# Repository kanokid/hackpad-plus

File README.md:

# Hackpad+
This is a hackpad that I made for Blueprint.
* It uses the Seeed Studio XIAO RP2040
* It has per-key shine through RGB
* It has 9 MX style switches and a rotary encoder for media controls/volume.
* The keys are through a 
* It uses KMK configured through pog for the firmware

Schematic:

PCB:

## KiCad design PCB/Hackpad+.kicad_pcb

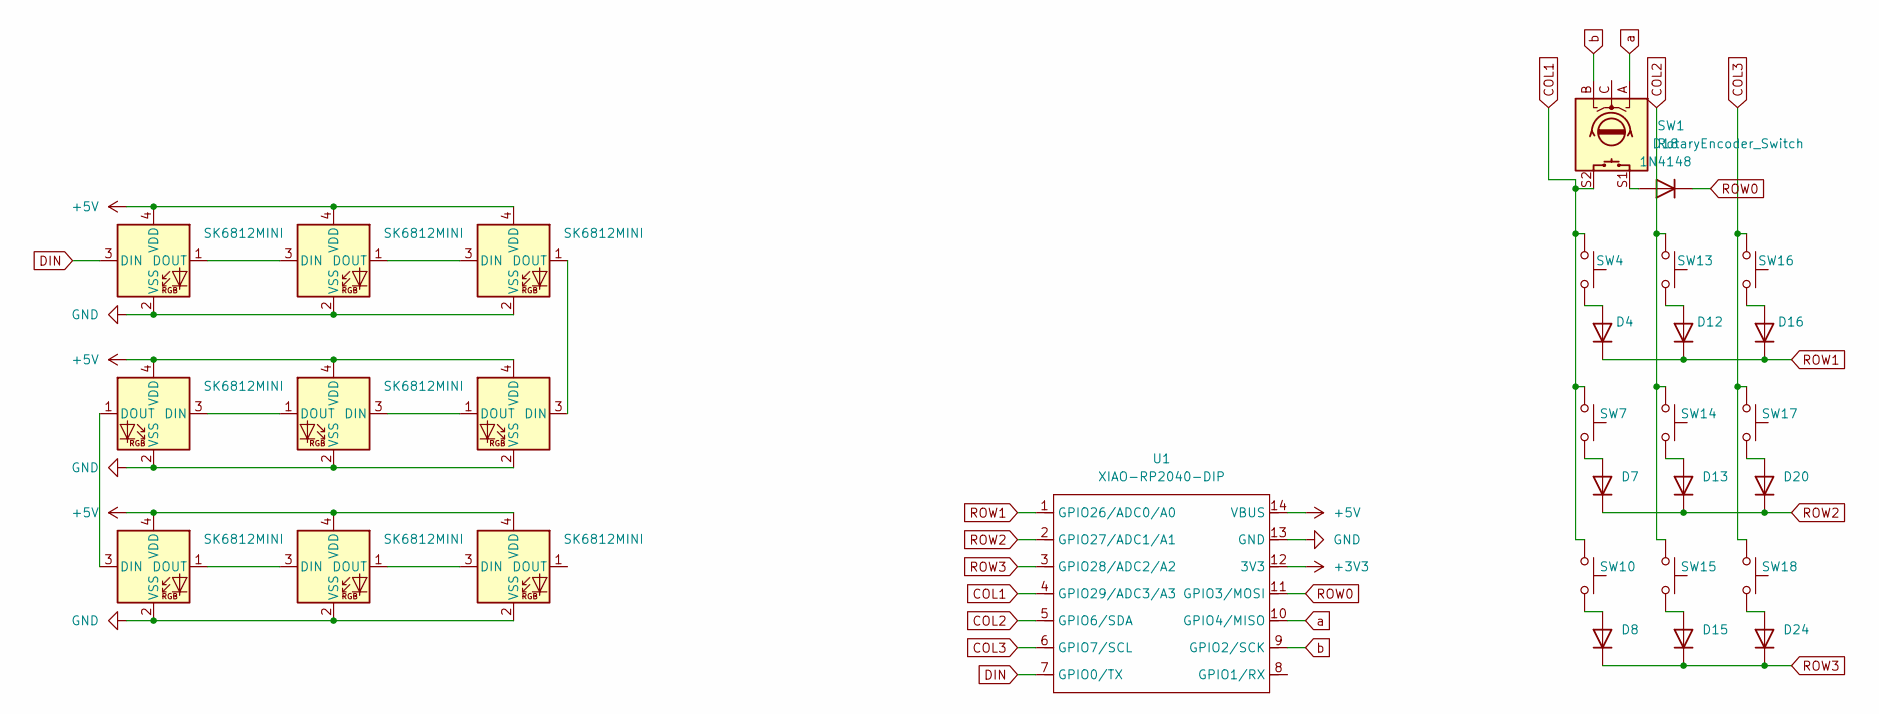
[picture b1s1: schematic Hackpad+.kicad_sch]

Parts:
D1, D2, D3, D5, D6, D9, D10, D11, D14: SK6812MINI; MX_SK6812MINI-E
D4, D7, D8, D12, D13, D15, D16, D18, D20, D24: 1N4148; D_DO-35_SOD27_P7.62mm_Horizontal
SW1: RotaryEncoder_Switch; RotaryEncoder_Alps_EC11E-Switch_Vertical_H20mm
SW4, SW7, SW10, SW13, SW14, SW15, SW16, SW17, SW18: SW_Push; SW_Cherry_MX_1.00u_PCB
U1: XIAO-RP2040-DIP

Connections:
+3V3: U1.12 (3V3)
+5V: D1.4 (VDD), D2.4 (VDD), D3.4 (VDD), D5.4 (VDD), D6.4 (VDD), D9.4 (VDD), D10.4 (VDD), D11.4 (VDD), D14.4 (VDD), U1.14 (VBUS)
COL1: SW1.S2, SW4.1, SW7.1, SW10.1, U1.4 (GPIO29/ADC3/A3)
COL2: SW13.1, SW14.1, SW15.1, U1.5 (GPIO6/SDA)
COL3: SW16.1, SW17.1, SW18.1, U1.6 (GPIO7/SCL)
DIN: D1.3 (DIN), U1.7 (GPIO0/TX)
GND: D1.2 (VSS), D2.2 (VSS), D3.2 (VSS), D5.2 (VSS), D6.2 (VSS), D9.2 (VSS), D10.2 (VSS), D11.2 (VSS), D14.2 (VSS), U1.13 (GND)
unnamed: D1.1 (DOUT), D2.3 (DIN)
unnamed: D2.1 (DOUT), D9.3 (DIN)
unnamed: D3.3 (DIN), D9.1 (DOUT)
unnamed: D4.2 (A), SW4.2
unnamed: D5.1 (DOUT), D6.3 (DIN)
unnamed: D7.2 (A), SW7.2
unnamed: D8.2 (A), SW10.2
unnamed: D3.1 (DOUT), D10.3 (DIN)
unnamed: D10.1 (DOUT), D14.3 (DIN)
unnamed: D6.1 (DOUT), D11.3 (DIN)
unnamed: D12.2 (A), SW13.2
unnamed: D13.2 (A), SW14.2
unnamed: D5.3 (DIN), D14.1 (DOUT)
unnamed: D15.2 (A), SW15.2
unnamed: D16.2 (A), SW16.2
unnamed: D18.2 (A), SW1.S1
unnamed: D20.2 (A), SW17.2
unnamed: D24.2 (A), SW18.2
ROW0: D18.1 (K), U1.11 (GPIO3/MOSI)
ROW1: D4.1 (K), D12.1 (K), D16.1 (K), U1.1 (GPIO26/ADC0/A0)
ROW2: D7.1 (K), D13.1 (K), D20.1 (K), U1.2 (GPIO27/ADC1/A1)
ROW3: D8.1 (K), D15.1 (K), D24.1 (K), U1.3 (GPIO28/ADC2/A2)
a: SW1.A, U1.10 (GPIO4/MISO)
b: SW1.B, U1.9 (GPIO2/SCK)

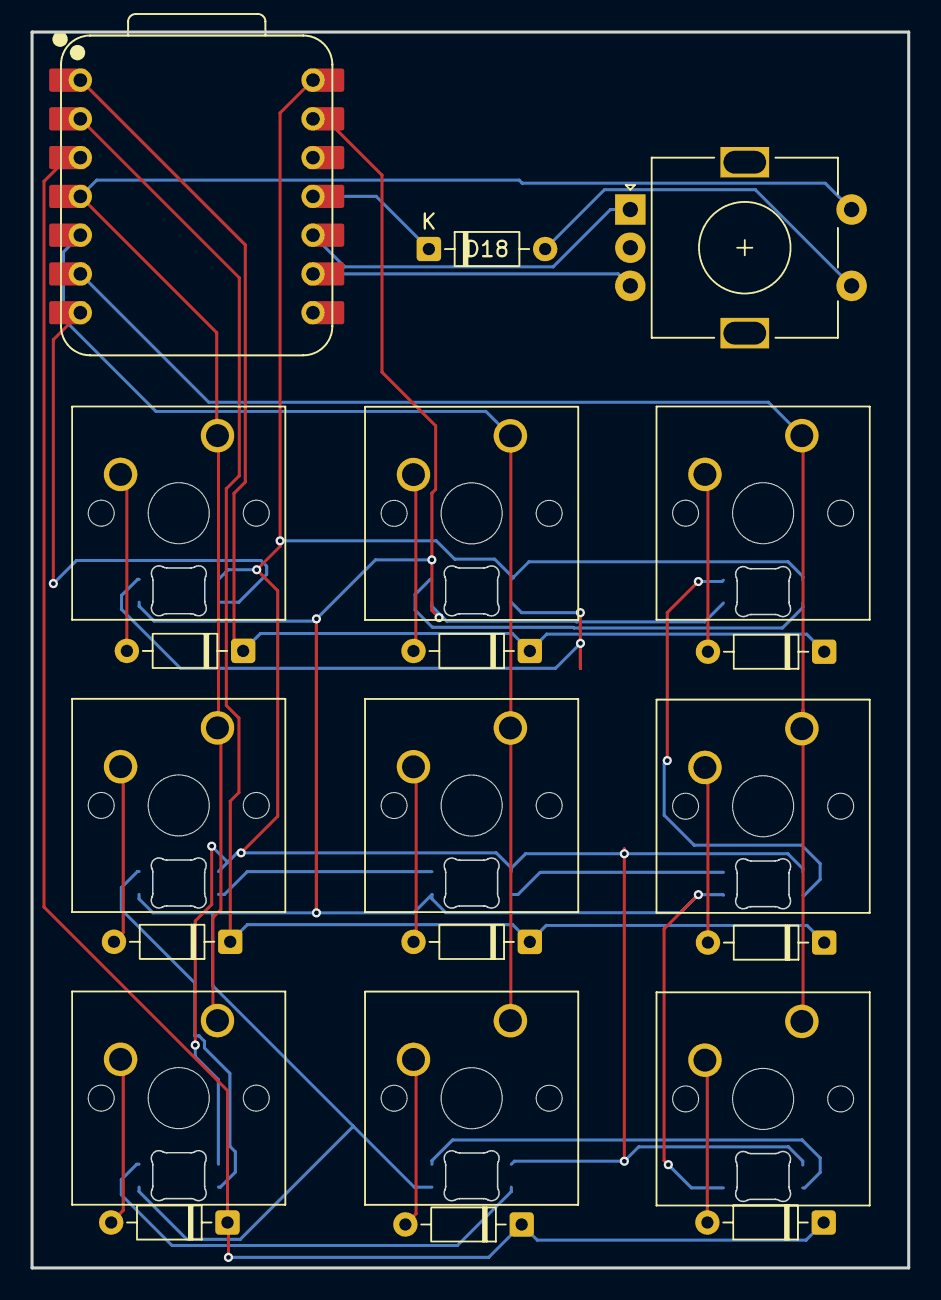
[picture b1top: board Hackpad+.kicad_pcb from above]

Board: 2 copper layers, 57.4 x 81.0 mm, 30 parts (0 on the bottom side), 30 nets.

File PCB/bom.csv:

Designator,Footprint,Quantity,Value,LCSC Part #
"D1, D10, D11, D14, D2, D3, D5, D6, D9",MX_SK6812MINI-E,9,SK6812MINI,
"D12, D13, D15, D16, D18, D20, D24, D4, D7, D8",D_DO-35_SOD27_P7.62mm_Horizontal,10,1N4148,
SW1,RotaryEncoder_Alps_EC11E-Switch_Vertical_H20mm,1,RotaryEncoder_Switch,
"SW10, SW13, SW14, SW15, SW16, SW17, SW18, SW4, SW7",SW_Cherry_MX_1.00u_PCB,9,SW_Push,
U1,XIAO-RP2040-DIP,1,XIAO-RP2040-DIP,

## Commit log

2026-04-01 added files
2026-04-01 Update README with schematic and PCB images
    Added schematic and PCB images to the README.
2026-04-01 changed files
2026-04-01 Add PCB image to README
    Added a new PCB image to the README.
2026-04-01 edit
